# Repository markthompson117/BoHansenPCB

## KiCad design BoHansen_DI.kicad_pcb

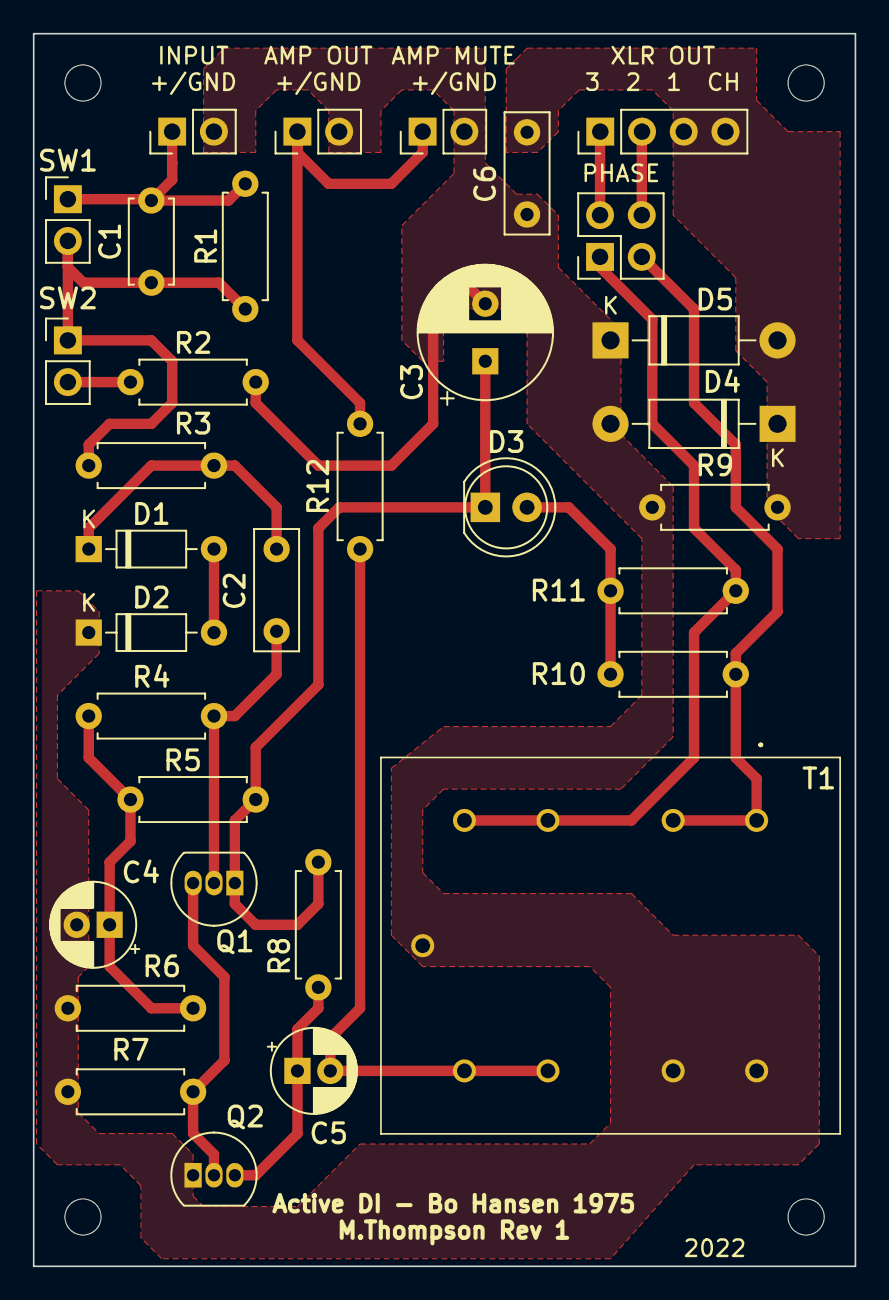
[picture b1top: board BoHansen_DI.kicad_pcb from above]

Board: 2 copper layers, 50.0 x 75.0 mm, 37 parts (0 on the bottom side), 19 nets.

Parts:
C1: 18p; C_Disc_D5.0mm_W2.5mm_P5.00mm
C2, C6: 100n; C_Rect_L7.2mm_W2.5mm_P5.00mm_FKS2_FKP2_MKS2_MKP2
C3: 100u; CP_Radial_D8.0mm_P3.50mm
C4, C5: 10u; CP_Radial_D5.0mm_P2.00mm
D1, D2: D_Zener; D_DO-35_SOD27_P7.62mm_Horizontal
D3: LED; LED_D5.0mm
D4, D5: 1N4004; D_DO-41_SOD81_P10.16mm_Horizontal
H1, H2, H3, H4: MountingHole; MountingHole_2.2mm_M2
J1: Input; PinHeader_1x02_P2.54mm_Vertical
J2: Amp out; PinHeader_1x02_P2.54mm_Vertical
J3: XLR out; PinHeader_1x04_P2.54mm_Vertical
Q1: BC550; TO-92_Inline
Q2: BC560; TO-92_Inline
R1: 2M2; R_Axial_DIN0207_L6.3mm_D2.5mm_P7.62mm_Horizontal
R2: 330k; R_Axial_DIN0207_L6.3mm_D2.5mm_P7.62mm_Horizontal
R3, R12: 10k; R_Axial_DIN0207_L6.3mm_D2.5mm_P7.62mm_Horizontal
R4: 1M; R_Axial_DIN0207_L6.3mm_D2.5mm_P7.62mm_Horizontal
R5, R6, R7: 100k; R_Axial_DIN0207_L6.3mm_D2.5mm_P7.62mm_Horizontal
R8: 3k9; R_Axial_DIN0207_L6.3mm_D2.5mm_P7.62mm_Horizontal
R9: 100R; R_Axial_DIN0207_L6.3mm_D2.5mm_P7.62mm_Horizontal
R10, R11: 6k8; R_Axial_DIN0207_L6.3mm_D2.5mm_P7.62mm_Horizontal
SW1, SW2: SW_SPST; PinHeader_1x02_P2.54mm_Vertical
SW3: Pol sw; PinHeader_2x02_P2.54mm_Vertical
SW4: Amp mute; PinHeader_1x02_P2.54mm_Vertical
T1: A262A3E

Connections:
GND1: C3.2, C4.2, C6.1, D2.1 (K), D4.2 (A), D5.1 (K), J1.2, J2.2, Q2.1 (C), R2.2, R6.2, R7.2, R9.2, SW4.2 (B), T1.B3 (SECONDARY_2_2), T1.B4 (SECONDARY_1_2), T1.MH1 (SCREEN)
GND2: C6.2, D4.1 (K), D5.2 (A), J3.3, J3.4, R9.1
unnamed: C1.1, R1.1, R3.2, SW1.2 (B), SW2.1 (A)
unnamed: C1.2, J1.1, R1.2, SW1.1 (A)
unnamed: C2.1, D1.1 (K), R3.1
unnamed: C2.2, Q1.2 (B), R4.2
unnamed: C3.1, D3.1 (K), Q1.1 (C), R5.2, R8.2
unnamed: C4.1, R4.1, R5.1, R6.1
unnamed: C5.1, Q2.3 (E), R8.1
unnamed: C5.2, R12.1, T1.B1 (SECONDARY_2_1), T1.B2 (SECONDARY_1_1)
unnamed: D1.2 (A), D2.2 (A)
unnamed: D3.2 (A), R10.2, R11.2
unnamed: J2.1, R12.2, SW4.1 (A)
unnamed: J3.1, SW3.2
unnamed: J3.2, SW3.4
unnamed: Q1.3 (E), Q2.2 (B), R7.1
unnamed: R2.1, SW2.2 (B)
unnamed: R10.1, SW3.3, T1.A1 (PRIMARY_1_1), T1.A2 (PRIMARY_2_1)
unnamed: R11.1, SW3.1, T1.A3 (PRIMARY_1_2), T1.A4 (PRIMARY_2_2)

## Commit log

2022-04-10 commit of final PCB output
2022-04-10 added custom footprint lib to directory
